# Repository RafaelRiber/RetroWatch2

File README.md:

# Retro|Watch 2
 <p align="center">
 
 <em>Assembled Board</em>
 
## Short description
The Retro|Watch V2 is based around the HP QDSP-6064 Bubble display, used in 70s HP calculators like the [HP-35](https://en.wikipedia.org/wiki/HP-35). The display is controlled by an Atmel ATMega328U4 MCU with Arduino code and flashed with an Adafruit Feather 32U4 bootloader, and the time is kept by a Maxim DS3231 Real-Time Clock module, that stays connected to the LiPo battery at all times, keeping time even when the microcontroller and display are not powered.
This second version of the watch uses another microcontroller, the ATMega32U4, for USB capability, and a battery recharge circuit for USB Charging. In order to fit all that added circuitry, smaller components as 0603 resistors and a QFN chip were used. **__THIS MAKES ASSEMBLY CONSIDERABLY HARDER THAN V1, and is not recommended for beginners.__**
The code is open source, licensed under the MIT License, and the harware is open-source hardware.

<h3>V1 was Featured on:</h3>
<p><a href="http://hackaday.com/2016/06/25/easy-bubble-watch-oozes-retro-charm/">Hackaday.com blog post by Elliot Williams</a>
<p><a href="https://blog.hackster.io/this-watch-will-spark-some-old-school-calculator-nostalgia-7b6e44203b67">Hackster.io</a>
  
## Hardware
<h3>PCB</h3>
The board design was made in Eagle, and is fully tested. A 500 mAh [LiPo Battery from Adafruit](https://adafru.it/1578) fits perfectly under the board. The board design can be freely modified. It can also directly be ordered on the OSHPark website: 
<p align="center"><a href="https://oshpark.com/shared_projects/D0Ed6ISU"></img></a></p>

<h3>Bill Of Materials</h3>
You can find the BOM here: https://github.com/RafaelRiber/Retro-Watch2/blob/master/Hardware/BOM.csv
  
<h2>Software</h2>
The software was written in Arduino code, is licensed under MIT License, and can be uploaded on the microcontroller via ISP.
Be sure to set the desired time in the code prior to uploading, to set the time registers on the RTC.

Functions of the code include:
* Hours, minutes and seconds
* Day, month, year, day of year, day in week, week in year.
* Stopwatch (start, stop, reset)
* Brightness setting in software, saved to EEPROM to save even if the watch is powered off.
* Battery voltage check and low battery alert
 
To be able to upload the code on the watch, you will need to follow the same steps as V1 (see V1 repo), but using the Adafruit Feather 32U4 Bootloader instead of the ATMega328P one.
<h3>Required Libraries</h3>
<p>1. Chrono library by thomasfredericks: https://github.com/thomasfredericks/Chrono
<p>2. Button library by JChristensen: https://github.com/JChristensen/Button
<p>3. RTCLib by Adafruit Industries: https://github.com/adafruit/RTClib
<p>4. SevSeg by SparkFun: https://github.com/sparkfun/SevSeg

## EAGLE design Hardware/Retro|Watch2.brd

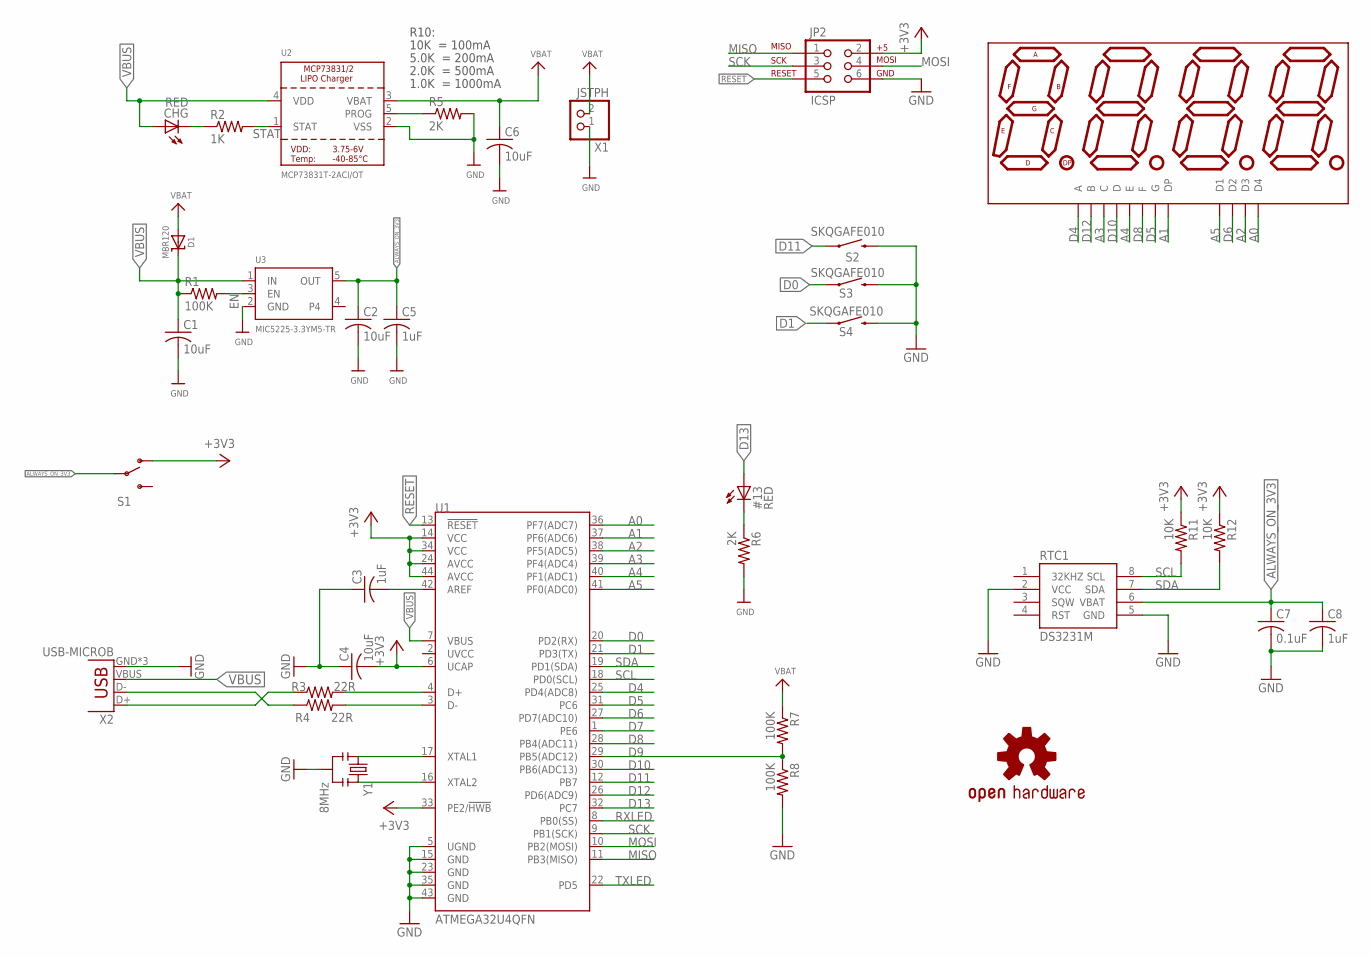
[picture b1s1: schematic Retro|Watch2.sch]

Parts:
#13: RED; CHIP-LED0805; MPN LGQ971
C1, C2, C6: 10uF; C0603; MPN MC0603X106M6R3CT
C3: 1uF; C0603; MPN 0805B104K500CT
C4: 10uF; C0603; MPN 0805B104K500CT
C5: 1uF; C0603; MPN CC0603MRY5V9BB104
C7: 0.1uF; C0603; MPN 0805B104K500CT
C8: 1uF; C0603; MPN 0603X105K100CT
CHG: RED; CHIP-LED0805; MPN LSQ976-Z
D1: MBR120; SOD-123; MPN MBR120VLSFT1G
DISP1: hp; DIL12
JP2: ICSP; 2X3_LOCK
LOGO1: OSHW-LOGOM-COPPER; OSHW-LOGO-M_COPPER
R1, R7, R8: 100K; R0603; MPN CRCW0603100KFKEA.
R2: 1K; R0603; MPN MC0063W06031221R
R3, R4: 22R; R0603; MPN CRCW060322R0FKEA
R5: 2K; R0603; MPN CRCW060310K0JNEA
R6: 2K; R0603; MPN CRCW06032K20JNEA
R11, R12: 10K; R0603; MPN CRCW060310K0FKEA
RTC1: DS3231M; SOIC8; MPN DS3231MZ+TRL
S1: SWITCH-SPDTSMD2; SWITCH-SPDT-SMD
S2, S3, S4: SKQGAFE010; TACTILE-SWITCH-SMD; MPN SKQGAFE010
U1: ATMEGA32U4QFN; QFN-44; MPN ATMEGA32U4-MU
U2: MCP73831T-2ACI/OT; SOT23-5@1; MPN MCP73831T-2ACI/OT
U3: MIC5225-3.3YM5-TR; SOT23-5; MPN MIC5225-3.3YM5-TR
X1: JSTPH; JSTPH2; MPN S2B-PH-SM4-TB(LF)(SN)
X2: USB-MICROB; MPN 10104110-0001LF
Y1: 8MHz; RESONATOR-SMD

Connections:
+3V3: C4.2, JP2.2, R11.1, R12.1, S1.1 (O), U1.6 (UCAP), U1.14 (VCC), U1.24 (AVCC), U1.33 (PE2/!HWB), U1.34 (VCC), U1.44 (AVCC)
A0: DISP1.6 (D4), U1.36 (PF7(ADC7))
A1: DISP1.5 (DP), U1.37 (PF6(ADC6))
A2: DISP1.4 (D3), U1.38 (PF5(ADC5))
A3: DISP1.3 (C), U1.39 (PF4(ADC4))
A4: DISP1.2 (E), U1.40 (PF1(ADC1))
A5: DISP1.1 (D1), U1.41 (PF0(ADC0))
ALWAYS_ON_3V3: C2.1, C5.1, C7.1, C8.1, RTC1.6 (VBAT), S1.2, U3.5 (OUT)
AREF: C3.2, U1.42 (AREF)
D0: S3.1, U1.20 (PD2(RX))
D1: S4.1, U1.21 (PD3(TX))
D4: DISP1.12 (A), U1.25 (PD4(ADC8))
D5: DISP1.7 (G), U1.31 (PC6)
D6: DISP1.10 (D2), U1.27 (PD7(ADC10))
D7: U1.1 (PE6)
D8: DISP1.9 (F), U1.28 (PB4(ADC11))
D9: R7.2, R8.1, U1.29 (PB5(ADC12))
D10: DISP1.8 (D), U1.30 (PB6(ADC13))
D11: S2.1, U1.12 (PB7)
D12: DISP1.11 (B), U1.26 (PD6(ADC9))
D13: #13.A, U1.32 (PC7)
D+: R3.1, X2.D+
D-: R4.1, X2.D-
EN: R1.2, U3.3 (EN)
GND: C1.2, C2.2, C3.1, C4.1, C5.2, C6.2, C7.2, C8.2, JP2.6, R5.2, R6.2, R8.2, RTC1.2 (VCC), RTC1.5 (GND), S2.3 (2), S3.3 (2), S4.3 (2), U1.5 (UGND), U1.15 (GND), U1.23 (GND), U1.35 (GND), U1.43 (GND), U2.2 (VSS), U3.2 (GND), X1.1, X2.GND, X2.MT1 (GND), X2.MT2 (GND), Y1.2
MISO: JP2.1, U1.11 (PB3(MISO))
MOSI: JP2.4, U1.10 (PB2(MOSI))
unnamed: U1.17 (XTAL1), Y1.1
unnamed: U1.16 (XTAL2), Y1.3
unnamed: R3.2, U1.4 (D+)
unnamed: R4.2, U1.3 (D-)
unnamed: CHG.C, R2.1
unnamed: #13.C, R6.1
PROG: R5.1, U2.5 (PROG)
RESET: JP2.5, U1.13 (!RESET)
RXLED: U1.8 (PB0(SS))
SCK: JP2.3, U1.9 (PB1(SCK))
SCL: R11.2, RTC1.8 (SCL), U1.18 (PD0(SCL))
SDA: R12.2, RTC1.7 (SDA), U1.19 (PD1(SDA))
STAT: R2.2, U2.1 (STAT)
TXLED: U1.22 (PD5)
VBAT: C6.1, D1.A, R7.1, U2.3 (VBAT), X1.2
VBUS: C1.1, CHG.A, D1.C, R1.1, U1.7 (VBUS), U2.4 (VDD), U3.1 (IN), X2.VBUS

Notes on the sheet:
10K = 100mA
5.0K = 200mA
2.0K = 500mA
1.0K = 1000mA
R10:

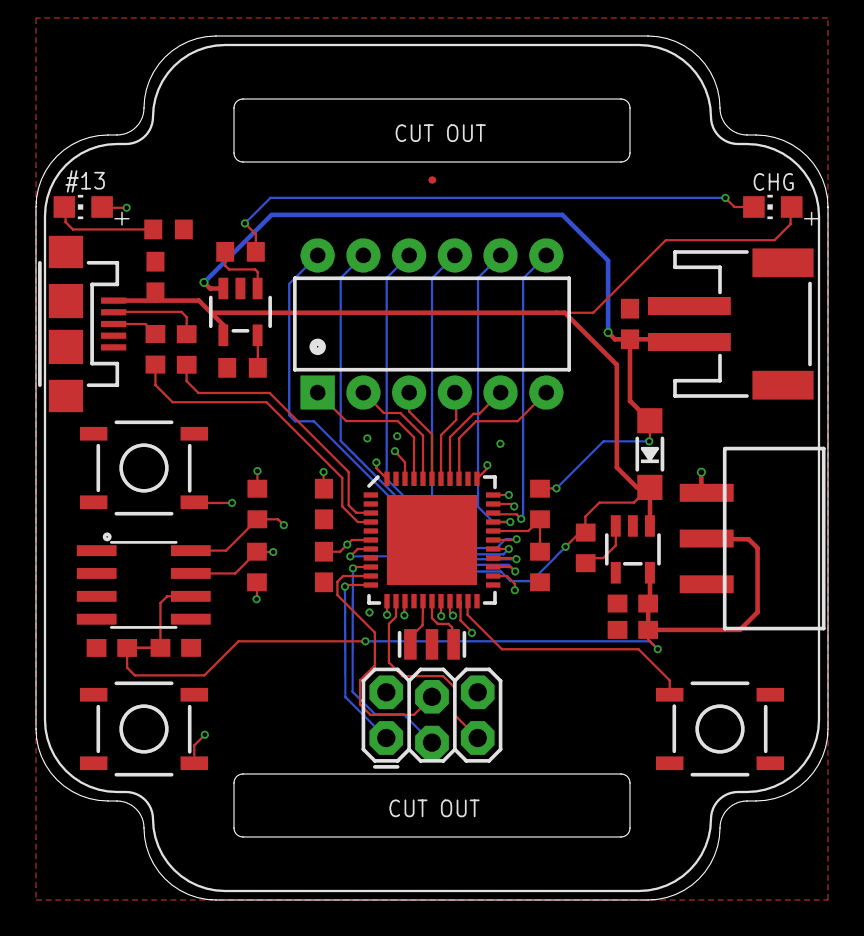
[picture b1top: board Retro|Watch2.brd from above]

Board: 4 copper layers, 44.0 x 48.0 mm, 35 parts (0 on the bottom side), 40 nets.

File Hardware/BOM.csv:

Qty;Value;Device;Package;Parts
1;0.1uF;C0603;C0603;C7
3;100K;R0603;R0603;R1, R7, R8
2;10K;R0603;R0603;R11, R12
4;10uF;C0603;C0603;C1, C2, C4, C6
1;1K;R0603;R0603;R2
3;1uF;C0603;C0603;C3, C5, C8
2;22R;R0603;R0603;R3, R4
2;2K;R0603;R0603;R5, R6
1;8MHz;RESONATOR SMD;RESONATOR-SMD;Y1
1;ATMEGA32U4-MU;MCU;QFN-44;U1
1;DS3231M;RTC;SOIC8;RTC1
1;MBR120;Schottky Diode;SOD-123;D1
1;MCP73831T-2ACI/OT;LiPoly Charger;SOT23-5;U2
1;MCS2S-A15F;SPDT Slide Switch;MCS2S-A15F;S1
1;MIC5225-3.3YM5-TR;Voltage Regulator 3.3V;SOT23-5;U3
1;USB-MICROB;USB Connector;USB-MICROB-SMD;X2

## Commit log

2016-08-26 Upload
2016-09-02 Uploaded
2018-09-15 Fixed formatting

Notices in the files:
parts and their libraries:
SparkFun-Displays: Licensing: Creative Commons ShareAlike 4.0 International - https://creativecommons.org/licenses/by-sa/4.0
microbuilder: This work is placed in the public domain, and may be freely used for commercial and non-commercial work with the following conditions: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
